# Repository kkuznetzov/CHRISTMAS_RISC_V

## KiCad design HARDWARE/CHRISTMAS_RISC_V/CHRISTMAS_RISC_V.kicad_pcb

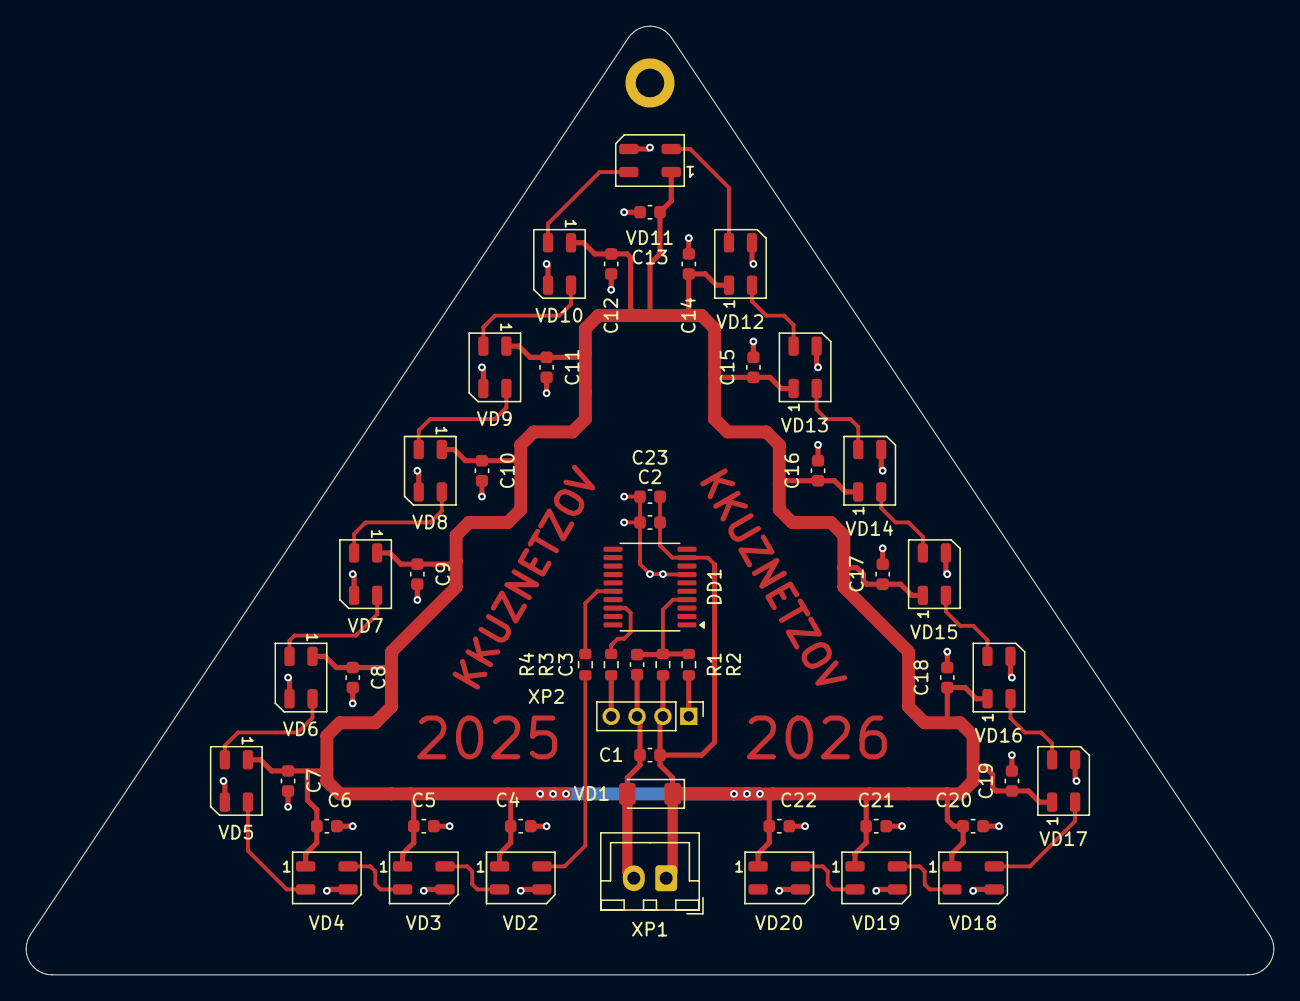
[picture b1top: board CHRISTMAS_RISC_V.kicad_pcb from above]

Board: 2 copper layers, 96.5 x 73.4 mm, 51 parts (0 on the bottom side), 26 nets.

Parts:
C1, C2, C3, C4, C5, C6, C7, C8, C9, C10, C11, C12, C13, C14, C15, C16, C17, C18, C19, C20, C21, C22: 0.1uF, 50V, X7R, 0603; C_0603_1608Metric
C23: 1uF, 25V, X5R, 0603; C_0603_1608Metric
DD1: CH32V003F4P6; TSSOP-20_4.4x6.5mm_P0.65mm
HOLE1: HOLE M2; MountingHole_2.2mm_M2_DIN965_Pad
R1: 10K, 1%, 0603; R_0603_1608Metric
R2, R3, R4: 27, 5%, 0603; R_0603_1608Metric
VD1: BZV55-B5V6; D_MiniMELF
VD2, VD3, VD4, VD5, VD6, VD7, VD8, VD9, VD10, VD11, VD12, VD13, VD14, VD15, VD16, VD17, VD18, VD19, VD20: WS2812B; LED_WS2812B-Mini_PLCC4_3.5x3.5mm
XP1: B2B-XH-A(LF)(SN); JST_XH_B2B-XH-A_1x02_P2.50mm_Vertical
XP2: PLS2-4; PinHeader_1x04_P2.00mm_Vertical

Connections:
/MOSI: DD1.16 (PC6), R4.1
/RESET: C3.2, DD1.4 (PD7), R1.2, R2.1
/RST_EXT: R2.2, XP2.1
/SWIO: DD1.18 (PD1), R3.1
/SWIO_EXT: R3.2, XP2.4
GND: C1.1, C2.1, C3.1, C4.2, C5.2, C6.2, C7.2, C8.2, C9.2, C10.2, C11.2, C12.2, C13.2, C14.2, C15.2, C16.2, C17.2, C18.2, C19.2, C20.2, C21.2, C22.2, C23.1, DD1.7 (VSS), VD1.2 (A), VD2.3 (VSS), VD3.3 (VSS), VD4.3 (VSS), VD5.3 (VSS), VD6.3 (VSS), VD7.3 (VSS), VD8.3 (VSS), VD9.3 (VSS), VD10.3 (VSS), VD11.3 (VSS), VD12.3 (VSS), VD13.3 (VSS), VD14.3 (VSS), VD15.3 (VSS), VD16.3 (VSS), VD17.3 (VSS), VD18.3 (VSS), VD19.3 (VSS), VD20.3 (VSS), XP1.2, XP2.3
unnamed: R4.2, VD2.4 (DIN)
unnamed: VD2.2 (DOUT), VD3.4 (DIN)
unnamed: VD3.2 (DOUT), VD4.4 (DIN)
unnamed: VD4.2 (DOUT), VD5.4 (DIN)
unnamed: VD5.2 (DOUT), VD6.4 (DIN)
unnamed: VD6.2 (DOUT), VD7.4 (DIN)
unnamed: VD7.2 (DOUT), VD8.4 (DIN)
unnamed: VD8.2 (DOUT), VD9.4 (DIN)
unnamed: VD9.2 (DOUT), VD10.4 (DIN)
unnamed: VD10.2 (DOUT), VD11.4 (DIN)
unnamed: VD11.2 (DOUT), VD12.4 (DIN)
unnamed: VD12.2 (DOUT), VD13.4 (DIN)
unnamed: VD13.2 (DOUT), VD14.4 (DIN)
unnamed: VD14.2 (DOUT), VD15.4 (DIN)
unnamed: VD15.2 (DOUT), VD16.4 (DIN)
unnamed: VD16.2 (DOUT), VD17.4 (DIN)
unnamed: VD17.2 (DOUT), VD18.4 (DIN)
unnamed: VD18.2 (DOUT), VD19.4 (DIN)
unnamed: VD19.2 (DOUT), VD20.4 (DIN)
VCC5V0: C1.2, C2.2, C4.1, C5.1, C6.1, C7.1, C8.1, C9.1, C10.1, C11.1, C12.1, C13.1, C14.1, C15.1, C16.1, C17.1, C18.1, C19.1, C20.1, C21.1, C22.1, C23.2, DD1.9 (VDD), R1.1, VD1.1 (K), VD2.1 (VDD), VD3.1 (VDD), VD4.1 (VDD), VD5.1 (VDD), VD6.1 (VDD), VD7.1 (VDD), VD8.1 (VDD), VD9.1 (VDD), VD10.1 (VDD), VD11.1 (VDD), VD12.1 (VDD), VD13.1 (VDD), VD14.1 (VDD), VD15.1 (VDD), VD16.1 (VDD), VD17.1 (VDD), VD18.1 (VDD), VD19.1 (VDD), VD20.1 (VDD), XP1.1, XP2.2

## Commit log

2025-12-26 Add documentation
2025-12-26 Add firmware
2025-12-26 Add hardware
